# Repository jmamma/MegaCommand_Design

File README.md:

# MegaCommand

## Description:

The MegaCommand is an open-source MIDI controller that runs the MCL firmware for use with the Elektron Machinedrum.
It is is based around the Arduino Mega 2560.

The printed cicuit board is a through-hole design (no SMD soldering skills required). 

* 4 x MIDI ports (2 in, 2 out)
* 4 x Rotary Encoders + Push button
* 4 x Buttons
* 1 x OLED display
* SD Card
* 128KBytes of SRAM (0-63KB accessible natively, 64-128KB accessible with bank selection)
* 2 x 10pin Expansion ports

Stack is 8KB in size. 
56KB of SRAM reserved for global objects, variables. (bank switchable)

The MCL respository contains the software component of this project.
https://github.com/jmamma/MCL

## Project Status:

Board revision: 1_0_2a12

__ALL INFORMATION BELOW IS PROVIDED AS A CONVENIENCE AND COULD BE SUBJECT TO ERROR OR CHANGE.__

## Bill of Materials:

1.0.2a:
https://github.com/jmamma/MegaCommand_Design/blob/master/1_0_2/bill_of_materials

## Display

OLED 128x32, it uses the SPI bus.

Important: OLED display requires resistor position changes to enable SPI mode as per adafruit documentation 
https://learn.adafruit.com/2-3-monochrome-128x32-oled-display-module/assembly-1):

## PCB Fabrication:

You can easily get your own PCBs made.

[PCBWay.com fabrication options](https://github.com/jmamma/MegaCommand_Design/blob/master/pcb_fabrication_preferences.jpg)

Gerber files (pcb layout diagrams used for fabrication) are included in the ./gerber/ directory above.

Download gerbers and submit to PCB manufacturer.

Circuit Schematic and Board Layout is present in Eagle files.

## Enclosure:

1.0.2a:

The enclosure can be 3D printed. The design files and variations are located in:

https://github.com/jmamma/MegaCommand_Design/tree/master/Enclosure/OLED/3D

Optionally print 4 spacers and superglue to the screw holes on the OLED to ease
installation of the screen at the proper height.

## Build Instructions

The build is organised in to multiple stages. You must follow the order sequentially.
At the end of each stage there is a test checkpoint. It is important that you perform these tests to ensure
each stage is working before proceeding to the next, failing to do so will make troubleshooting any problems much harder.

```
VERIFY CHIP ORIENTATION BEFORE SOLDERING.

OLED display must be installed last.

Take care in making sure the ICs are inserted the correct way around.

## Build Order: 

  1. ICS: RAM, Octal Latch, Shift Registers
  2. Arduino male headers. 
  3. Capacitors. (Make sure the 220uF electrolytic cap fits when the arduino is connected)
                 (10uF +ve terminal is soldered to pad closest to SD card holder.
                 
TEST POINT: Run the SRAM firmware test.

  4. MEC switches (Make sure these sit completely flush with the board and are not leaning to one side)
  5. Resistor arrays
  6. Encoders (Make sure these sit completely flush with the board and are not leaning to one side)  
  
TEST POINT: Run the button and encoder test firmware.
  7. ICS: MIDI Optocouplers. 
  8. Resistors + diodes
  9. MIDI DIN ports.
 
TEST POINT: Run the MIDIPort test firmware.

 10. Power Jack (+9V tip)
 11. Yamaichi SD card holder.
     
TEST POINT: Insert SD Card, Run the SDCARD test firmware
 
OLED Display:
 12. Oled display requires correct resistor poisiton in order to be configured for SPI mode. (See documentation above to confirm the resistor placement)
 13. Male header to be soldered to OLED board. Header is then soldered on to MegaCommand PCB. The height of the OLED display is important. The distance between the mainboard pcb, and the bottom on the OLED pcb should be 5mm when soldered.
 
 14. LEDs (+ anode pin nearest to the bottom of the board for both LEDs. ). When soldered, the tip of the LED should measure 11mm above mainboard pcb.
 
 15. Power switch. (optional, you can solder a short between the two right most pins on EG1212B  
 
 Expansion Headers:
 
 16. These are short 5mm headers. It might not be possible to buy them at the right length so you'll need to cut them down to 10 pin.
 
TEST POINT: Run the LCD and LED test firmware.

## Important

OLED Display must be installed last.

5) To install the male headers that connect to the MegaCommand to the ArduinoMega, insert the headers in to the ArduinoMega then solder with the arduino attached to the headers. This will ensure perfect alignment.
```

## Firmware

Once you've built a MegaCommand you can upload the latest version of the  MCL firmware located here: 
https://github.com/jmamma/MCL/releases

If you're familiar with coding you can write sketches within the Arduino IDE to test the hardware and run custom firmwware.
Before you start coding you need to decide which core you are going to use.

## Arduino Cores
In ArduinoIDE, a Core is a collection of initialisation functions and associated libraries, used for configuring the underlying hardware; it is analogous to an Operating System kernel.

The cores availabile in the Arduino IDE are listed under Tools -> Boards.

Arduino Mega or Mega 2560:

This is the standard core that comes installed default with the Arduino IDE. If you use this core with the MegaCommand you can program the MegaCommand like an ordinary arduino shield. The built in arduino functions can be used to control the hardware using the pin assignement detailed below.

MCL Core:

This was built on top of Manuel Odendahl's core for the MiniCommand.
By using this core you can take advantage of the powerful MIDI libraries and GUI functionality.

For example, the MegaCommand core is necessary for running the MCL firmware, and controlling the Elektron instrument range.

### Installing the MCL core.
(Instructions for OSX, should be similar for Windows)

1) Download the Arduino IDE https://www.arduino.cc/en/Main/Software (1.8.5 tested)

2) Get the MIDICtrl library and MegaCommand Core (same repo):
```
   cd /Applications/Arduino.app/Contents/Java/hardware/
   git clone https://github.com/jmamma/MCL
```
### Selecting the Core

1) Open the Arduino IDE, Under the Tools menu, select the core you wish to use from the "Board:" menu

The default Arduino core is named "Arduino/Genuino Mega or Mega 2560"

The MegaCommand core will be listed at the bottom. 

## MegaCommand vs MiniCommand

The MegaCommand shield was designed to be backwards compatible with the original MiniCommand hardware. 

However, there are notable differences between the two systems, including new pin assignments which must be taken account for when using the original MidiCtrl libraries.

The original MiniCommand used the ATMega64 microprocessor whilst the MegaCommand Shield is built on top of ArduinoMega which uses the ATMega2560 processor. The ATMega2560 shares most of the IO functionality of the ATMega64 but has additional pins, and a different pin-to-port layout.

The MegaCommand Shield accesses the ATMega2560 processor on board the ArduinoMega through the exposed headers, not all pins on the ATMega2560 are exposed through this Arduino interface.

Incorporating the differences between both processors and subsequent pin availability the following pin assignment has been made as the best possible substitutes for the original hardware layout.

```
4 Midi Ports vs 3
256k ROM vs 64K
USB vs No USB

--

MegaCommand pin changes from original MiniCommand are as followed:

MicroSD board:

CS = PB0

SRAM

BankSel = PL6

Key Scanning (Shift Register Circuit):

PL0 = OUT
PL1 = SHIFT
PL2 = CLK

HD44780 LCD Circuit:

E = PL4
R/S = PL3

LEDs:

PE5 = LED0
PE4 = LED1

MIDI:

TXD0 and RXD0 (USART0) are reserved for Arduino USB interface.

Therefore we shift midi ports by 1.

MIDI Port 1:

RXD1 = MIDI Port 1 IN.
TXD1 = MIDI Port 1 OUT

Midi Port 2:

RXD2 = MIDI Port 2 IN
TXD2 = MIDI Port 2 OUT ( New port, not available on original Minicommand)
```

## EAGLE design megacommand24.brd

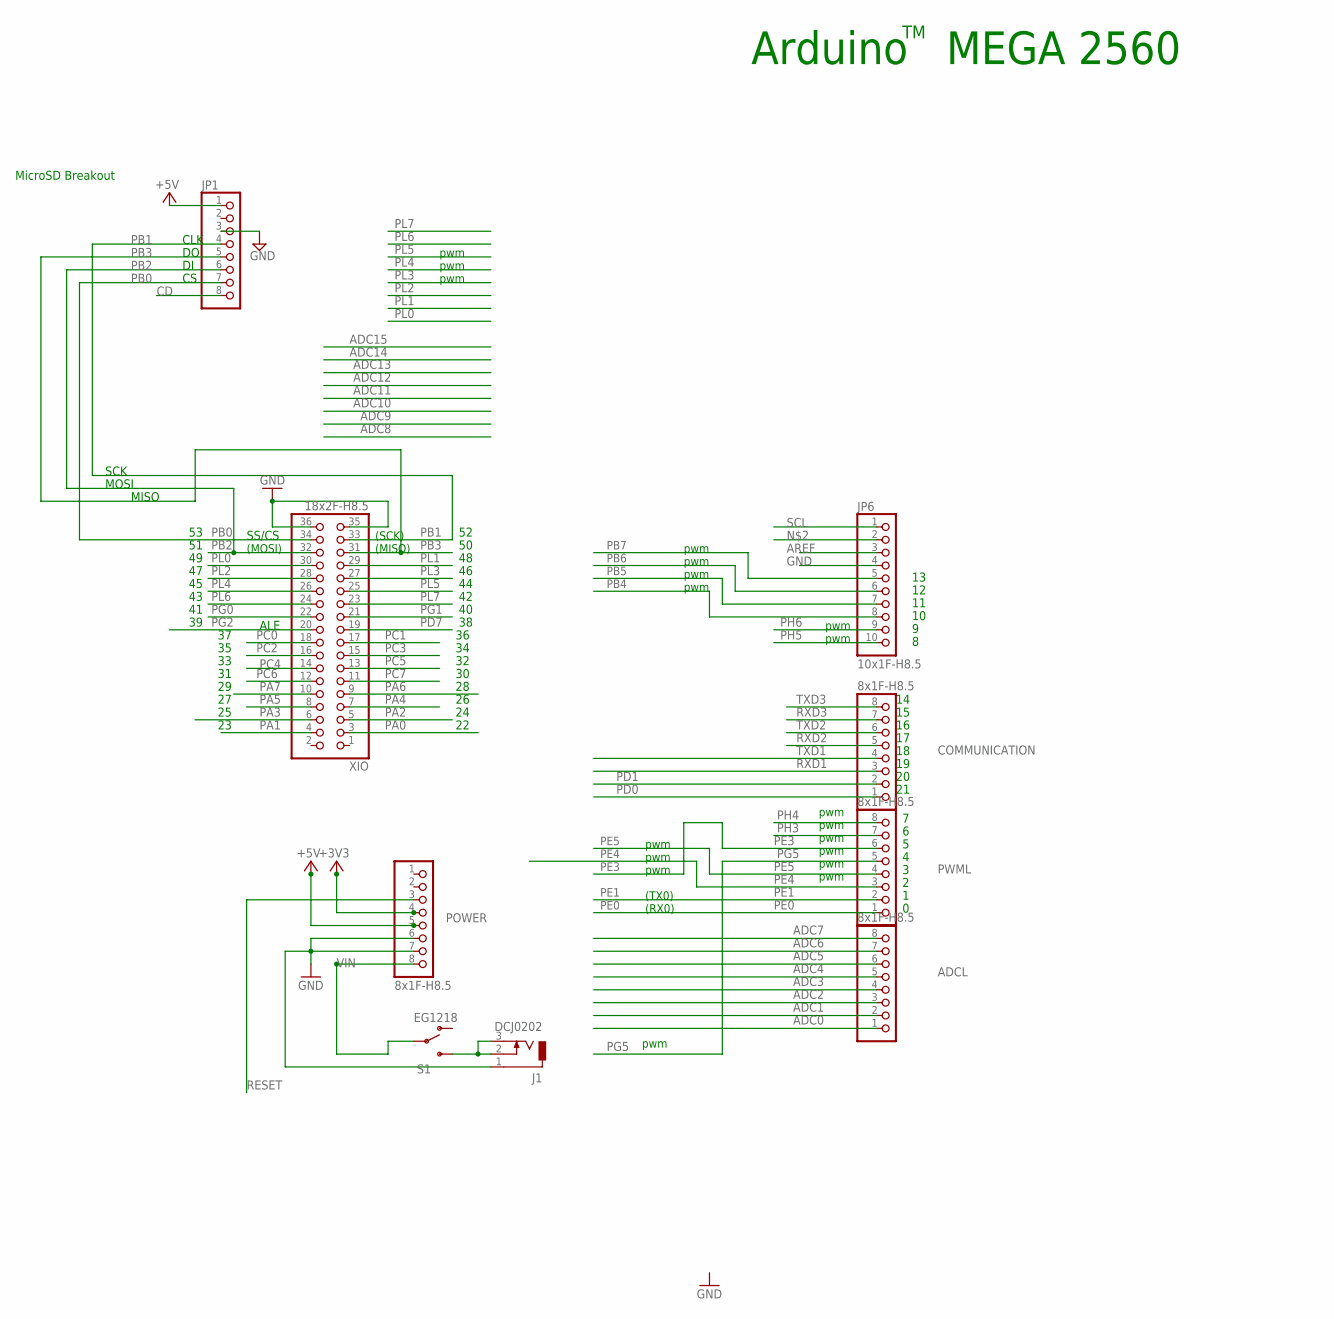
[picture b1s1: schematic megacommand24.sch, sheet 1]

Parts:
ADCL: 8x1F-H8.5; 1X08
COMMUNICATION: 8x1F-H8.5; 1X08
J1: DCJ0202
JP1: PINHD-1X8BIG; 1X08-BIG
JP6: 10x1F-H8.5; 1X10
POWER: 8x1F-H8.5; 1X08
PWML: 8x1F-H8.5; 1X08
S1: EG1218; SWITCH-SPDT_KIT
XIO: 18x2F-H8.5; 2X18

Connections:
+3V3: POWER.4; also elsewhere on the board
+5V: JP1.1, POWER.5; also elsewhere on the board
ADC0: ADCL.1; also elsewhere on the board
ADC1: ADCL.2; also elsewhere on the board
ADC2: ADCL.3; also elsewhere on the board
ADC3: ADCL.4; also elsewhere on the board
ADC4: ADCL.5
ADC5: ADCL.6
ADC6: ADCL.7
ADC7: ADCL.8
AREF: JP6.3
CD: JP1.8
GND: J1.1, JP1.3, JP6.4, POWER.6, POWER.7, XIO.35, XIO.36; also elsewhere on the board
unnamed: J1.2, J1.3, S1.3 (S)
PA0: XIO.3; also elsewhere on the board
PA1: XIO.4; also elsewhere on the board
PA2: XIO.5; also elsewhere on the board
PA3: XIO.6; also elsewhere on the board
PA4: XIO.7; also elsewhere on the board
PA5: XIO.8; also elsewhere on the board
PA6: XIO.9; also elsewhere on the board
PA7: XIO.10; also elsewhere on the board
PB0: JP1.7, XIO.34
PB1: JP1.4, XIO.33; also elsewhere on the board
PB2: JP1.6, XIO.32; also elsewhere on the board
PB3: JP1.5, XIO.31
PB4: JP6.8
PB5: JP6.7
PB6: JP6.6
PB7: JP6.5
PC0: XIO.18; also elsewhere on the board
PC1: XIO.17; also elsewhere on the board
PC2: XIO.16; also elsewhere on the board
PC3: XIO.15; also elsewhere on the board
PC4: XIO.14; also elsewhere on the board
PC5: XIO.13; also elsewhere on the board
PC6: XIO.12; also elsewhere on the board
PC7: XIO.11; also elsewhere on the board
PD0: COMMUNICATION.1
PD1: COMMUNICATION.2
PD7: XIO.19; also elsewhere on the board
PE0: PWML.1
PE1: PWML.2
PE3: PWML.6
PE4: PWML.3; also elsewhere on the board
PE5: PWML.4; also elsewhere on the board
PG0: XIO.22; also elsewhere on the board
PG1: XIO.21; also elsewhere on the board
PG2: XIO.20; also elsewhere on the board
PG5: PWML.5
PH3: PWML.7
PH4: PWML.8
PH5: JP6.10
PH6: JP6.9
PL0: XIO.30; also elsewhere on the board
PL1: XIO.29; also elsewhere on the board
PL2: XIO.28; also elsewhere on the board
PL3: XIO.27; also elsewhere on the board
PL4: XIO.26; also elsewhere on the board
PL5: XIO.25; also elsewhere on the board
PL6: XIO.24; also elsewhere on the board
PL7: XIO.23; also elsewhere on the board
RESET: POWER.3
RXD1: COMMUNICATION.3; also elsewhere on the board
RXD2: COMMUNICATION.5; also elsewhere on the board
RXD3: COMMUNICATION.7
SCL: JP6.1
TXD1: COMMUNICATION.4; also elsewhere on the board
TXD2: COMMUNICATION.6; also elsewhere on the board
TXD3: COMMUNICATION.8
VIN: POWER.8, S1.2

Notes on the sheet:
Arduino MEGA 2560
pwm
(TX0)
(RX0)
(MOSI)
(SCK)
(MISO)
ALE
SS/CS
SCK
MOSI
MISO
CLK
MicroSD Breakout

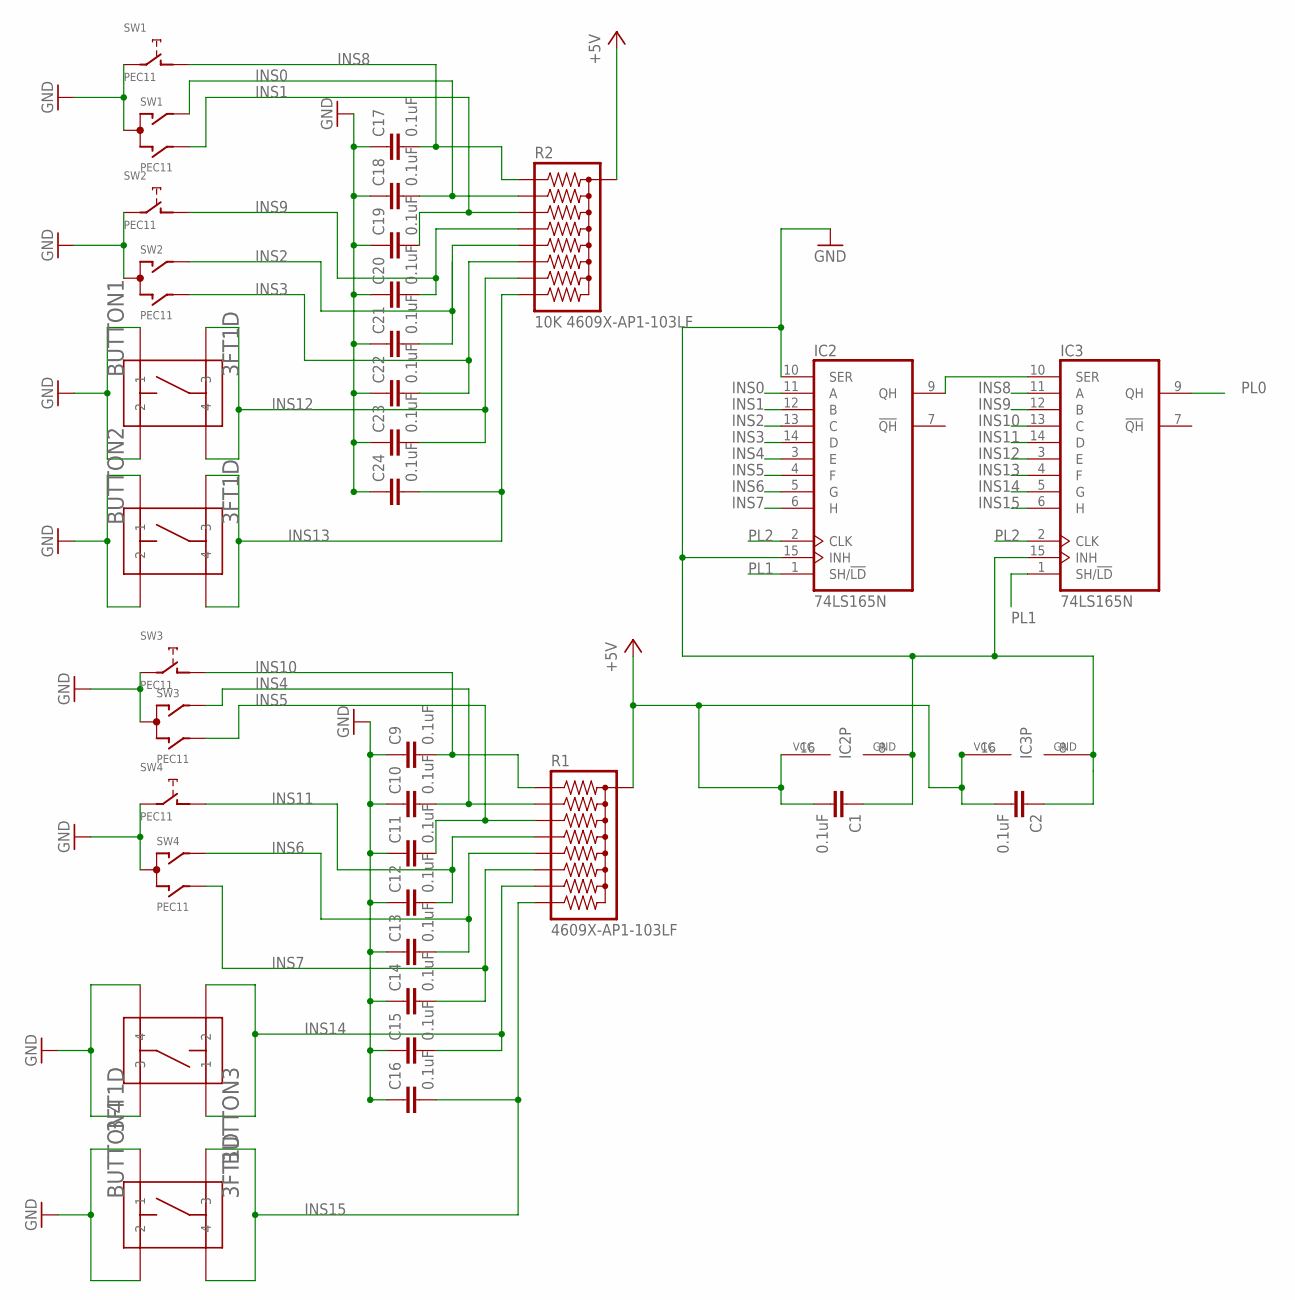
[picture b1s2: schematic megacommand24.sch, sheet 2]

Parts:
BUTTON1, BUTTON2, BUTTON3, BUTTON4: 3FT1D; 3FT
C1, C2, C9, C10, C11, C12, C13, C14, C15, C16, C17, C18, C19, C20, C21, C22, C23, C24: 0.1uF; C025-050X050
IC2, IC3: 74LS165N; DIL16
R1: 4609X-AP1-103LF; RPACK-SIP-PTH-8
R2: 10K 4609X-AP1-103LF; RPACK-SIP-PTH-8
SW1, SW2, SW3, SW4: PEC11; ALPS_EC12E_SW

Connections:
+5V: C1.2, C2.2, IC2.16 (VCC), IC3.16 (VCC), R1.P$1 (1), R2.P$1 (1); also elsewhere on the board
GND: BUTTON1.P$1 (1), BUTTON1.P$2 (2), BUTTON2.P$1 (1), BUTTON2.P$2 (2), BUTTON3.P$3 (3), BUTTON3.P$4 (4), BUTTON4.P$1 (1), BUTTON4.P$2 (2), C1.1, C2.1, C9.1, C10.1, C11.1, C12.1, C13.1, C14.1, C15.1, C16.1, C17.1, C18.1, C19.1, C20.1, C21.1, C22.1, C23.1, C24.1, IC2.8 (GND), IC2.10 (SER), IC2.15 (INH), IC3.8 (GND), IC3.15 (INH), SW1.C, SW1.E (2), SW2.C, SW2.E (2), SW3.C, SW3.E (2), SW4.C, SW4.E (2); also elsewhere on the board
INS0: C18.2, IC2.11 (A), R2.P$3 (3), SW1.A
INS1: C19.2, IC2.12 (B), R2.P$4 (4), SW1.B
INS2: C21.2, IC2.13 (C), R2.P$6 (6), SW2.A
INS3: C22.2, IC2.14 (D), R2.P$7 (7), SW2.B
INS4: C10.2, IC2.3 (E), R1.P$3 (3), SW3.A
INS5: C11.2, IC2.4 (F), R1.P$4 (4), SW3.B
INS6: C13.2, IC2.5 (G), R1.P$6 (6), SW4.A
INS7: C14.2, IC2.6 (H), R1.P$7 (7), SW4.B
INS8: C17.2, IC3.11 (A), R2.P$2 (2), SW1.D (1)
INS9: C20.2, IC3.12 (B), R2.P$5 (5), SW2.D (1)
INS10: C9.2, IC3.13 (C), R1.P$2 (2), SW3.D (1)
INS11: C12.2, IC3.14 (D), R1.P$5 (5), SW4.D (1)
INS12: BUTTON1.P$3 (3), BUTTON1.P$4 (4), C23.2, IC3.3 (E), R2.P$8 (8)
INS13: BUTTON2.P$3 (3), BUTTON2.P$4 (4), C24.2, IC3.4 (F), R2.P$9 (9)
INS14: BUTTON3.P$1 (1), BUTTON3.P$2 (2), C15.2, IC3.5 (G), R1.P$8 (8)
INS15: BUTTON4.P$3 (3), BUTTON4.P$4 (4), C16.2, IC3.6 (H), R1.P$9 (9)
unnamed: IC2.9 (QH), IC3.10 (SER)
PL0: IC3.9 (QH); also elsewhere on the board
PL1: IC2.1 (SH/!LD), IC3.1 (SH/!LD); also elsewhere on the board
PL2: IC2.2 (CLK), IC3.2 (CLK); also elsewhere on the board

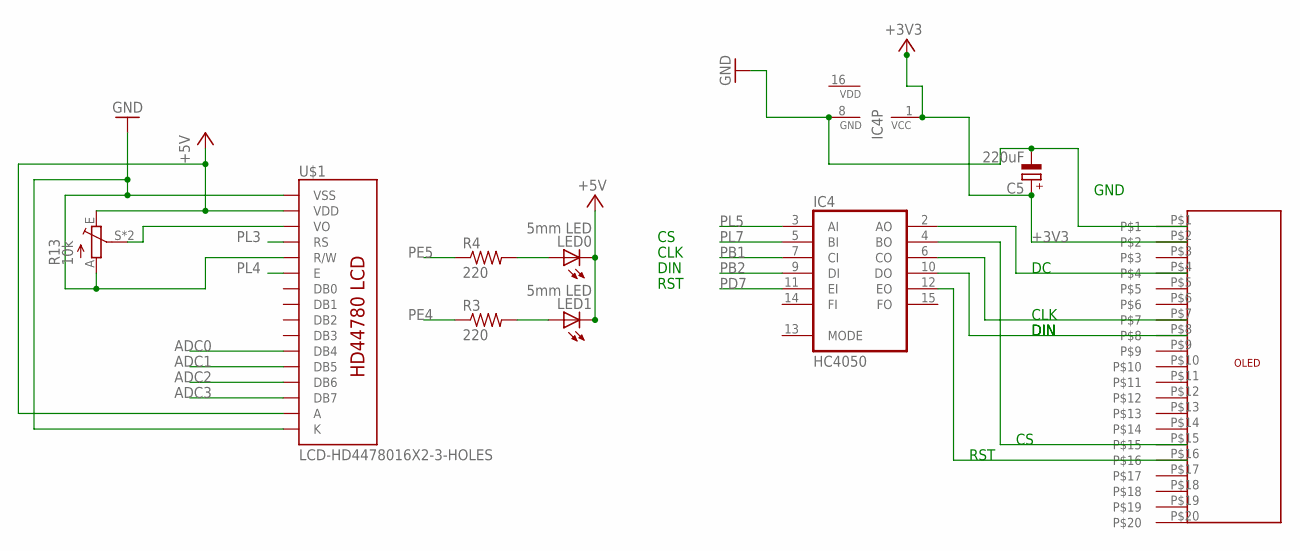
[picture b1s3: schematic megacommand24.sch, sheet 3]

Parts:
C5: 220uF; TT2D6
IC4: HC4050; DIL16
LED0, LED1: 5mm LED; LED_LD260
R3, R4: 220; 0207/7
R13: 10k; CA6V
U$1: LCD-HD4478016X2-3-HOLES; LCD-16X2-3HOLES
U$2: 20PIN

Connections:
+3V3: C5.+, IC4.1 (VCC), U$2.P$2; also elsewhere on the board
+5V: LED0.K (C), LED1.K (C), R13.E, U$1.2 (VDD), U$1.15 (A); also elsewhere on the board
ADC0: U$1.11 (DB4); also elsewhere on the board
ADC1: U$1.12 (DB5); also elsewhere on the board
ADC2: U$1.13 (DB6); also elsewhere on the board
ADC3: U$1.14 (DB7); also elsewhere on the board
GND: C5.-, IC4.8 (GND), R13.A, U$1.1 (VSS), U$1.5 (R/W), U$1.16 (K), U$2.P$1; also elsewhere on the board
unnamed: LED0.A, R4.2
unnamed: LED1.A, R3.2
unnamed: IC4.2 (AO), U$2.P$4
unnamed: R13.S, R13.S1 (S), U$1.3 (VO)
unnamed: IC4.6 (CO), U$2.P$7
unnamed: IC4.10 (DO), U$2.P$8
unnamed: IC4.4 (BO), U$2.P$15
unnamed: IC4.12 (EO), U$2.P$16
PB1: IC4.7 (CI); also elsewhere on the board
PB2: IC4.9 (DI); also elsewhere on the board
PD7: IC4.11 (EI); also elsewhere on the board
PE4: R3.1; also elsewhere on the board
PE5: R4.1; also elsewhere on the board
PL3: U$1.4 (RS); also elsewhere on the board
PL4: U$1.6 (E); also elsewhere on the board
PL5: IC4.3 (AI); also elsewhere on the board
PL7: IC4.5 (BI); also elsewhere on the board
VDD: IC4.16 (VDD)

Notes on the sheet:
GND
RST
CLK
DIN

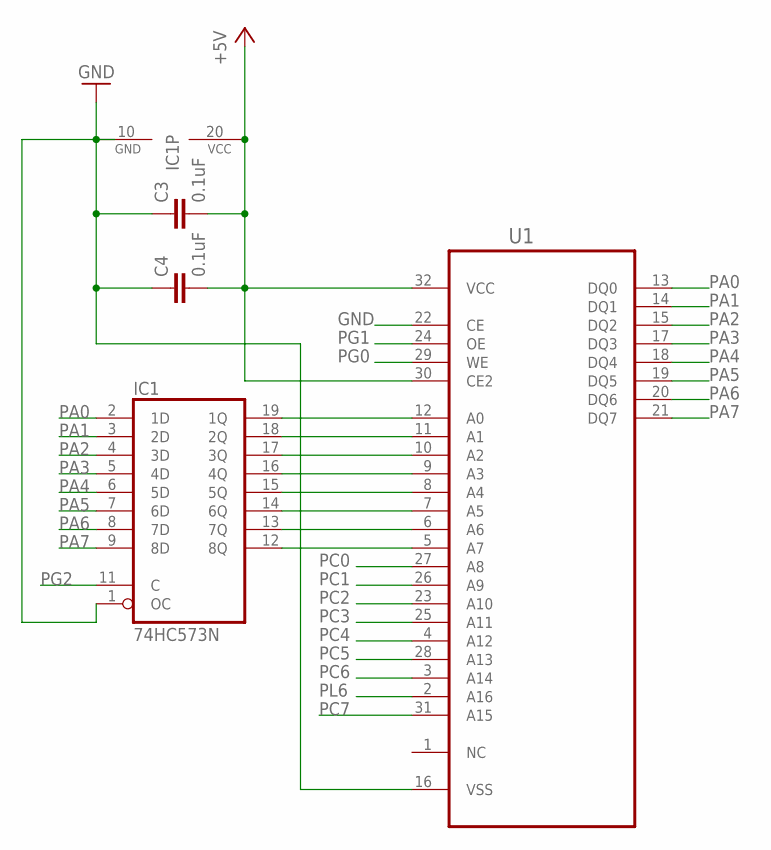
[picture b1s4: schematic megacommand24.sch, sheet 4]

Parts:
C3, C4: 0.1uF; C025-050X050
IC1: 74HC573N; DIL20
U1: AS6C1008-55PCN; DIP254P1524X393-32

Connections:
+5V: C3.2, C4.2, IC1.20 (VCC), U1.30 (CE2), U1.32 (VCC); also elsewhere on the board
GND: C3.1, C4.1, IC1.1 (OC), IC1.10 (GND), U1.16 (VSS), U1.22 (CE); also elsewhere on the board
unnamed: IC1.13 (7Q), U1.6 (A6)
unnamed: IC1.19 (1Q), U1.12 (A0)
unnamed: IC1.18 (2Q), U1.11 (A1)
unnamed: IC1.17 (3Q), U1.10 (A2)
unnamed: IC1.16 (4Q), U1.9 (A3)
unnamed: IC1.15 (5Q), U1.8 (A4)
unnamed: IC1.14 (6Q), U1.7 (A5)
unnamed: IC1.12 (8Q), U1.5 (A7)
PA0: IC1.2 (1D), U1.13 (DQ0); also elsewhere on the board
PA1: IC1.3 (2D), U1.14 (DQ1); also elsewhere on the board
PA2: IC1.4 (3D), U1.15 (DQ2); also elsewhere on the board
PA3: IC1.5 (4D), U1.17 (DQ3); also elsewhere on the board
PA4: IC1.6 (5D), U1.18 (DQ4); also elsewhere on the board
PA5: IC1.7 (6D), U1.19 (DQ5); also elsewhere on the board
PA6: IC1.8 (7D), U1.20 (DQ6); also elsewhere on the board
PA7: IC1.9 (8D), U1.21 (DQ7); also elsewhere on the board
PC0: U1.27 (A8); also elsewhere on the board
PC1: U1.26 (A9); also elsewhere on the board
PC2: U1.23 (A10); also elsewhere on the board
PC3: U1.25 (A11); also elsewhere on the board
PC4: U1.4 (A12); also elsewhere on the board
PC5: U1.28 (A13); also elsewhere on the board
PC6: U1.3 (A14); also elsewhere on the board
PC7: U1.31 (A15); also elsewhere on the board
PG0: U1.29 (WE); also elsewhere on the board
PG1: U1.24 (OE); also elsewhere on the board
PG2: IC1.11 (C); also elsewhere on the board
PL6: U1.2 (A16); also elsewhere on the board

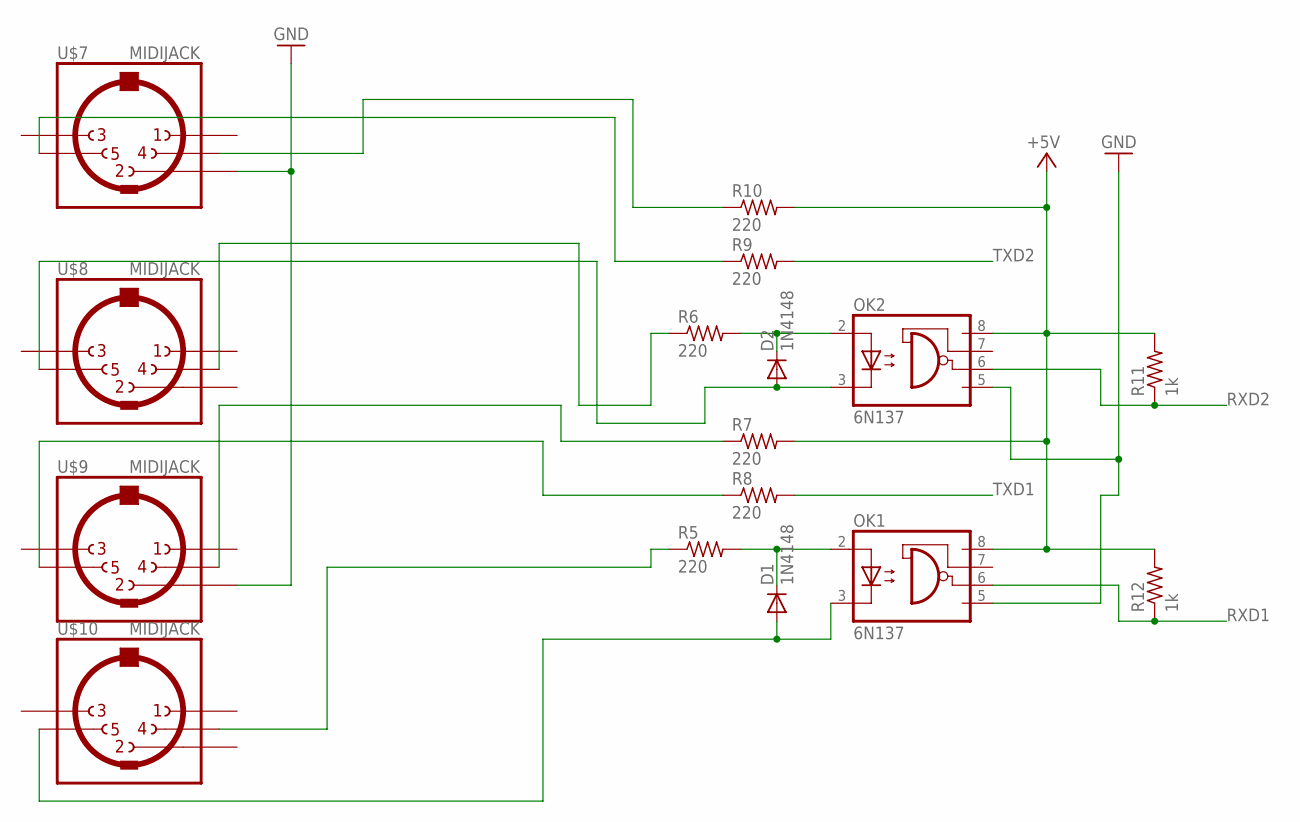
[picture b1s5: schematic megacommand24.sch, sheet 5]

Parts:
D1, D2: 1N4148; DO35-7
OK1, OK2: 6N137; DIL08
R5, R6, R7, R8, R9, R10: 220; 0207/7
R11, R12: 1k; 0207/7
U$7, U$8, U$9, U$10: MIDIJACK; CP-2350

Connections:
+5V: OK1.8 (VCC), OK2.8 (VCC), R7.2, R10.2, R11.2, R12.2; also elsewhere on the board
GND: OK1.5 (GND), OK2.5 (GND), U$7.2, U$9.2; also elsewhere on the board
unnamed: R8.1, U$9.5
unnamed: D1.A, OK1.3 (C), U$10.5
unnamed: R5.1, U$10.4
unnamed: R7.1, U$9.4
unnamed: R10.1, U$7.4
unnamed: D2.C, OK2.2 (A), R6.2
unnamed: D2.A, OK2.3 (C), U$8.5
unnamed: R6.1, U$8.4
unnamed: R9.1, U$7.5
unnamed: D1.C, OK1.2 (A), R5.2
RXD1: OK1.6 (VO), R12.1; also elsewhere on the board
RXD2: OK2.6 (VO), R11.1; also elsewhere on the board
TXD1: R8.2; also elsewhere on the board
TXD2: R9.2; also elsewhere on the board

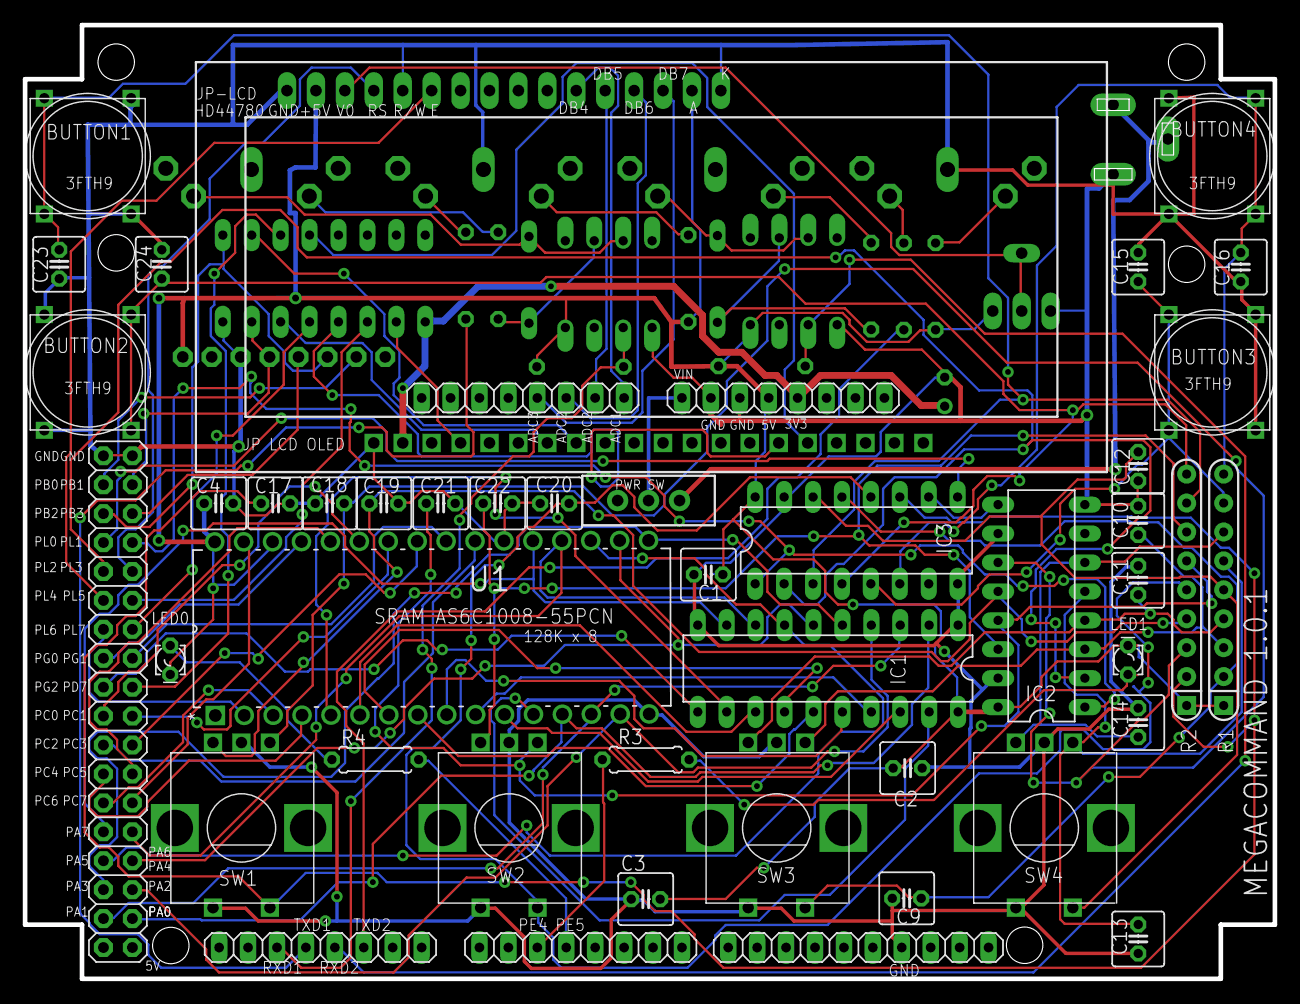
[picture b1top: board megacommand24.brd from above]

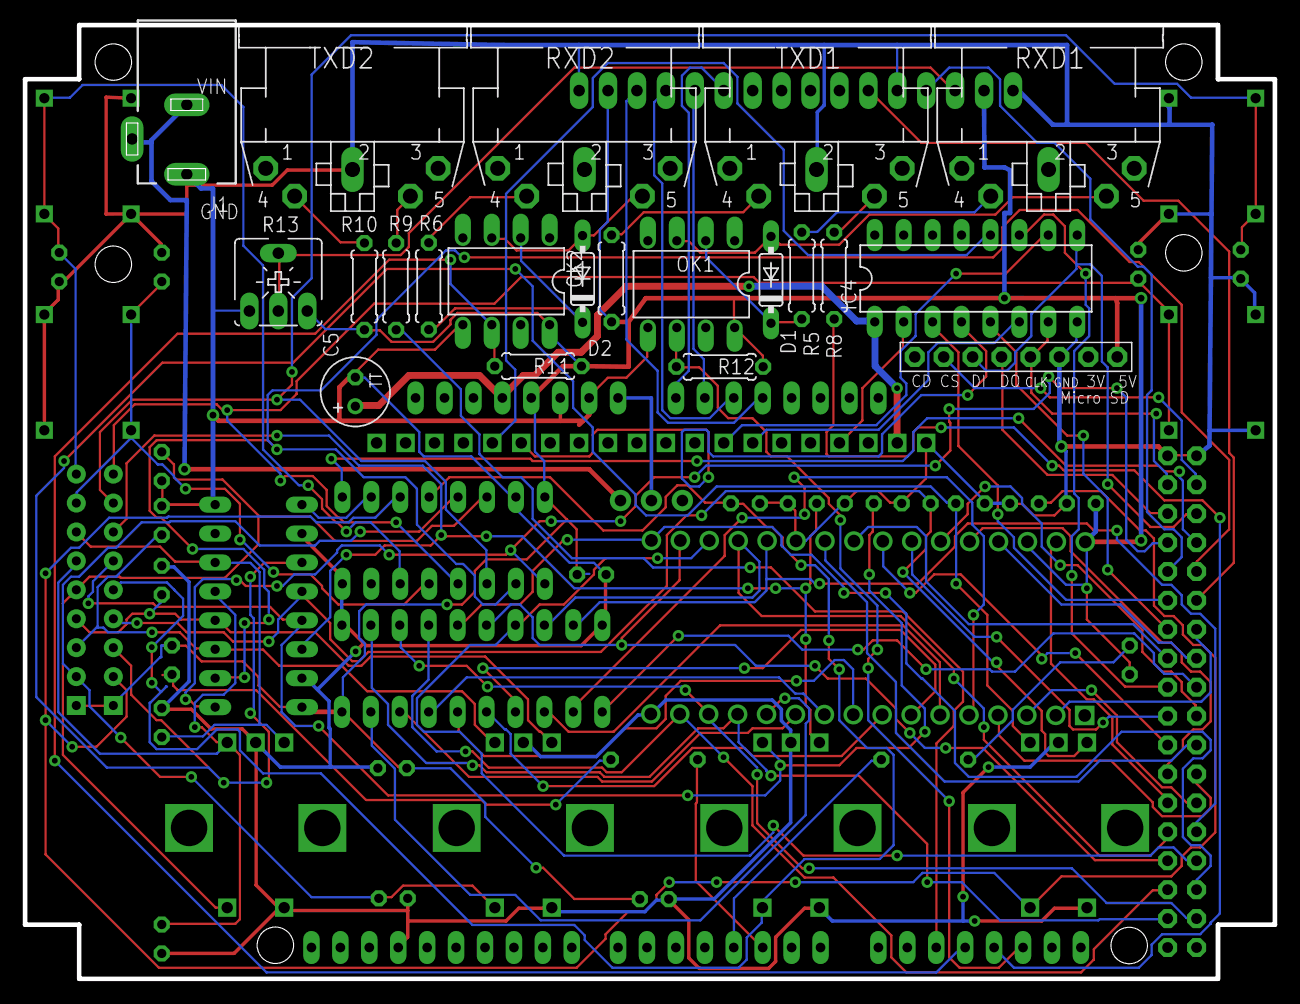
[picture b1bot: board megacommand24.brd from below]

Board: 2 copper layers, 109.8 x 83.8 mm, 68 parts (21 on the bottom side), 90 nets.

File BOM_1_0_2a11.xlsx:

STACKABLE ARDUINO HEADERS MALE 13mm Length:
1 |  | PINHD-1X8BIG | X08-BIG | JP1 | PIN HEADER
1 | 20PIN | 20PIN | 20PIN | U$2
4 | 8x1-H8.5 | PINHD-1X8 | 1X08 | ADCL, COMMUNICATION, POWER, PWML | PIN HEADER
1 | 18x2-H8.5 | PINHD-2X18 | 2X18 | XIO | PIN HEADER
1 | 10x1-H8.5 | PINHD-1X10_ARD | 1X10 | JP6 | PIN HEADER
ARDUINO MINI HEADERS FEMALE (5mm height).
2 | PINHD-1X10 |  |  | EXP_L, EXP_R | Pin header 1x10 0.1" spacing
1 | PINHD-1X3 |  |  |  | POWER SWITCH RAISER.
POWER JACK 2 PIN:
1 | POWER_JACKPTH_LOCK | 490-PJ-037A | POWER_JACK_PTH_LOCK | J1 | Power Jack
CAPS:
21 | 0.1uF | 75-1C10Z5U104M050B | C025-050X050 | C1, C2, C3, C4, C6, C9, C10, C11, C12, C13, C14, C15, C16, C17, C18, C19, C20, 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 | CAPACITOR, European symbol
1 | 10uF | ECE-A1CKA100I | C025-050X050 | C7 | CAPACITOR, European symbol
1 | 220uF | 271-220-RC | TT2D6 | C5 | POLARIZED CAPACITOR, European symbol
RESISTORS:
2 | 10K | 4609X-AP1-103LF | RPACK-BUSSED-8-SIP-PTH-8 | R1, R2
2 | 1k | 271-1K-RC | 0207/7 | R11, R12 | RESISTOR, American symbol
8 | 220 | R-US_0207/7 | 0207/7 | R3, R4, R5, R6, R7, R8, R9, R10 | RESISTOR, American symbol
Diodes:
2 | 1N4148 | 1N4148DO35-7 | DO35-7 | D1, D2 | DIODE
2 | 5mm LED | HLMP-1301 | LED_LD260 | LED0, LED1 | LED
OptoCoupler:
2 | 6N137 | 782-6N137 | DIL08 | OK1, OK2 | MOTOROLA OPTO COUPLER 6N137 1328376 52M1895
ICs:
1 | 74HC573N | 74HC573N | DIL20 | IC1 | 8-bit D latch BUS DRIVER
2 | 74LS165N | 74LS165N | DIL16 | IC2, IC3 | 8-bit parallel load SHIFT
1 | AS6C1008-55PCN | AS6C1008-55PCN | 128K SRAM | U1 | CMOS SRAM
1 | HC4050 | 4504N | DIL16 | IC4 | TTL or CMOS to CMOS hex LEV SHIFTER
MIDIJack:
4 | MIDIJACK | 490-SDS-50 | CP-2350 | U$7, U$8, U$9, U$10 | DIN 5 jack also known as MIDI jack
Switches:
1 | EG1218 | SWITCH-SPDTKIT | SWITCH-SPDT_KIT | S1
4 | 3F T1D | 3F T1D | 3FT | BUTTON1, BUTTON2, BUTTON3, BUTTON4 | Mulitmec - 3FT1D
4 | 642-1D09
Encoders:
4 | PEC11 | 652-PEC11R-4015F-S24 | ALPS_EC12E_SW | SW1, SW2, SW3, SW4 | ALPS rotary Encoder EC12E
1 | YAMAICHI_SD_CARD | YAMAICHI_SD_CARD | YAMAICHI_MICROSD_VERTICAL | PJS008U
OLED Display:
1 | 2.2INCH 128x32 OLED |  |  |  | w/ i2c, spi, ssd1305 controller, white-on-black | https://www.buydisplay.com/default/arduino-2-2-inch-128x32-o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
 |  |  |  |  |  | Or: https://item.taobao.com/item.htm?spm=a230r.1.14.128.4f6533ec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

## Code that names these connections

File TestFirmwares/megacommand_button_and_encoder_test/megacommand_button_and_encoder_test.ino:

//MegaCommand Button & Encoder Test Firmware
//Version 1.0
//Author: Justin Mammarella & Manuel Odendahl
//Date: Sept 2017
//Description: Firmware to test the encoders and switches on the MegaCommand hardware
//             Run this firmware by uploading to the MegaCommand and then viewing the output of Serial Monitor at 9600bps
//             By rotating encoders and pressing each button you should see the corresponding bits change in the serial monitor output.
//Notes:       This firmware uses the Arduino Core.

#define SET_BIT(port, bit)   ((port) |= (1 << (bit)))
#define CLEAR_BIT(port, bit) ((port) &= ~(1 << (bit)))
#define TOGGLE_BIT(port, bit) ((port) ^= (1 << (bit)))
#define IS_BIT_SET(port, bit) (((port) & (1 << (bit))) ? 1 : 0)
#define IS_BIT_CLEAR(port, bit) (((port) & (1 << (bit))) == 0 ? 1 : 0)

/** 8-bit macros. **/
#define SET_BIT8(port, bit)   ((port) |= (uint8_t)(1 << (bit)))
#define CLEAR_BIT8(port, bit) ((port) &= (uint8_t)~(1 << (bit)))
#define IS_BIT_SET8(port, bit) (((port) & (uint8_t)(1 << (bit))) ? 1 : 0)
#define IS_BIT_CLEAR8(port, bit) (((port) & (uint8_t)(1 << (bit))) == 0 ? 1 : 0)

#define SR165_OUT    PL0
#define SR165_SHLOAD PL1
#define SR165_CLK    PL2

#define SR165_DATA_PORT PORTL
#define SR165_DDR_PORT  DDRL
#define SR165_PIN_PORT  PINL

#define SR165_DELAY() { } // asm("nop"); } // asm("nop");  asm("nop");  }

void my_clk() {
  CLEAR_BIT8(SR165_DATA_PORT, SR165_CLK);
  SET_BIT8(SR165_DATA_PORT, SR165_CLK);
}

void my_rst() {
  CLEAR_BIT8(SR165_DATA_PORT, SR165_SHLOAD);
  SET_BIT8(SR165_DATA_PORT, SR165_SHLOAD);

}

void my_init() {
 SR165_DDR_PORT |= _BV(SR165_SHLOAD) | _BV(SR165_CLK);
  //   digitalWrite(SR165_SHLOAD, LOW);
  
  CLEAR_BIT8(SR165_DDR_PORT, SR165_OUT);
  CLEAR_BIT8(SR165_DATA_PORT, SR165_OUT);
  SET_BIT8(SR165_DATA_PORT, SR165_CLK);
  SET_BIT8(SR165_DATA_PORT, SR165_SHLOAD);
}

uint16_t my_read16() {
  my_rst();

  uint16_t res = 0;
  uint8_t i = 0;
  for (i = 0; i < 16; i++) {
    res <<= 1;
    res |= IS_BIT_SET8(SR165_PIN_PORT, SR165_OUT);
    my_clk();
  }

  return res;
}

/**********************************************/

void setup() {
//  pinMode(SR165_OUT, INPUT);
 // pinMode(SR165_CLK, OUTPUT);
 // pinMode(SR165_SHLOAD, OUTPUT);
   Serial.begin(9600);

my_init();
  // put your setup code here, to run once:

}
 uint16_t oldsr = 0;
void loop() {
  // put your main code here, to run repeatedly:
  
   uint16_t sr = my_read16();
   uint8_t count = 0;
   if (sr != oldsr) {

       for(uint8_t i=0; i< 16; i++)
    {
      
      Serial.print(sr >> i & 1, BIN);
      if (count < 8) {
      if (count % 2) { Serial.print(" "); }
      }
    
    else {
      Serial.print(" ");
    }
          count++;

    }
   
    Serial.print("\n");
   oldsr = sr;
}
   
}

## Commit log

2017-03-06 Adding files
2017-03-06 Readme fix
2017-03-23 3D Models of the 1590BB enclosuer with machining
2017-03-26 Enclosure modified for correct midi port placement. Material now also removed from lid. I've updated the eagle files for the new LCD placement. Pad size increased for encoders. Some capactiors moved 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
2017-04-02 MegaCommand 1.0.0c Gerber
2017-04-02 PCBWay fabrication preferences. Use these settings to fab your own boards
2017-04-02 MegaCommand 1_0_0c 3D models for printing or milling
2017-04-02 MegaCommand 1_0_0c board and schematic files
2017-04-02 update image
2017-04-02 preserve
2017-04-02 Removing old files
2017-04-02 MegaCommand Lid 1_0_0c
2017-04-03 bill of materials
2017-04-28 This revision includes an OLED Header and Level Shifter, the powerjack component has been replcaed as the pcbfootprint was incorrect
2017-05-06 Midi port size increased
2017-06-06 MegaCommand 1.0.1 . OLED added. Led position shifted. New footprint for DC jack. Complete re-route.
2017-06-07 Fix for GND rail
2017-06-26 cleanup
2017-06-26 cleanup 2
2017-06-26 readme
2017-06-26 Cleannup
2017-07-12 MegaCommand 1_0_1a Schematics + Gerbers. Correct OLED display port direction and added a 12bit SPI DAC
2017-08-14 added reference photography
2017-09-19 created gerber directory
2017-09-22 Added diagrams
2017-09-24 added SRAM Test firmware
2017-09-24 Added button_and_encoder test firmware
2017-09-24 added midiin test firmware
2017-09-24 added megacommand midiout test firmware
2017-09-24 added megacommand_led_test firmware
2017-09-24 added sdcard test firmware
2017-09-24 fixed directory paths
2017-09-24 removed ghost file
2017-09-24 added megacommand hd44780 display test firmware
2018-02-23 Bug fix, would try to read memory location above 0xFFFF and fail
2018-02-23 SDCard test now writes and verifies a 1MB random array
2018-04-20 Added eagle schematic and board for 1.0.2a11
2018-04-23 Create BOM_1_0_2a11
2018-04-23 Added 1_0_2_a12 gerbers
2018-04-23 Update BOM_1_0_2a11
2018-04-23 DC jack was on wrong side of board
2018-04-23 remove old files
2019-03-07 update BOM_1_0_2a11: reformatting
2019-03-12 directory restructure
2019-03-12 added reference photography for 1_0_2 design
2019-03-12 Added OLED enclosure design (thanks to Ozone)
2019-03-16 add OLED display test firmware
2019-03-16 TestFirmwares: sdcard test: fix initialization sequence
2019-03-16 TestFirmwares: sdcard test: reformat debug info
2019-04-02 add expansion port pin diagram
2019-04-09 Regenerated enclosure body in freecad.
    Had to turn the 590BB enclosure in to a "Solid" object before
    performing boolean cut operations.
    Regenerate the mesh STL. The 3D slicer is reporting 0 issues,
    which is a massive improvement.
2019-04-09 Added M3 square nut traps traps to the enclosure design
2019-04-10 Reduced OLED width slightly, created a taller version of the original model. Need to test both
2019-04-10 Update lid for tall model
2019-04-11 Increased trap height to 2mm, increased drill hole size, reduced body height by 2mm (Tall)
2019-04-14 Update lid, for tall enclosure. Has raised support for MIDI ports
2019-04-15 Removed nut traps, reverted screw size, reduced LED size, re-organised dir
2019-04-15 Drill hole radius consistant along depth
2019-04-15 rename folder
2019-04-16 Added printable encoder knobs
2019-04-16 Rounded upper edge of encoder
2019-04-19 Move lower buttons up by 0.5mm to match 1_0_2 board layout
2019-04-22 fix drill hole radius inconsistency along depth
2019-08-14 add assembled board model
2019-08-14 add assembled board model with arduino
2019-10-12 fix oled module dimensions, add other part STL models
2020-01-28 Update BOM_1_0_2a11
    While i was sourcing the components i corrected some few mistakes on the 1_0_2 BOM
2020-04-25 Update BOM_1_0_2a11
    update switch part number.
2020-05-03 Update README.md
    Make build instructions clearer.
2020-05-18 Fix typos in README
2020-08-14 Update megacommmand lid with shorter rise
2020-08-14 Remove old lid stl
2021-04-22 Improve BOM
2021-04-22 minor
2021-04-22 rm 1_0_1
2021-04-22 remove hd44780
2021-04-22 Update bill_of_materials
2021-09-09 Add additional testing stage to detect addressing problems
2021-11-06 License
2021-11-30 Add spacers for the OLED screen
2023-04-16 Add files via upload
    Files from Marcus B.
2023-05-01 Add MegaCMD non-diy enclosure stl files
2023-05-01 Add Pabloantxon designs
2023-05-01 folder renaming

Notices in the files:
parts and their libraries:
SparkFun-Resistors: Licensing: Creative Commons ShareAlike 4.0 International - https://creativecommons.org/licenses/by-sa/4.0
